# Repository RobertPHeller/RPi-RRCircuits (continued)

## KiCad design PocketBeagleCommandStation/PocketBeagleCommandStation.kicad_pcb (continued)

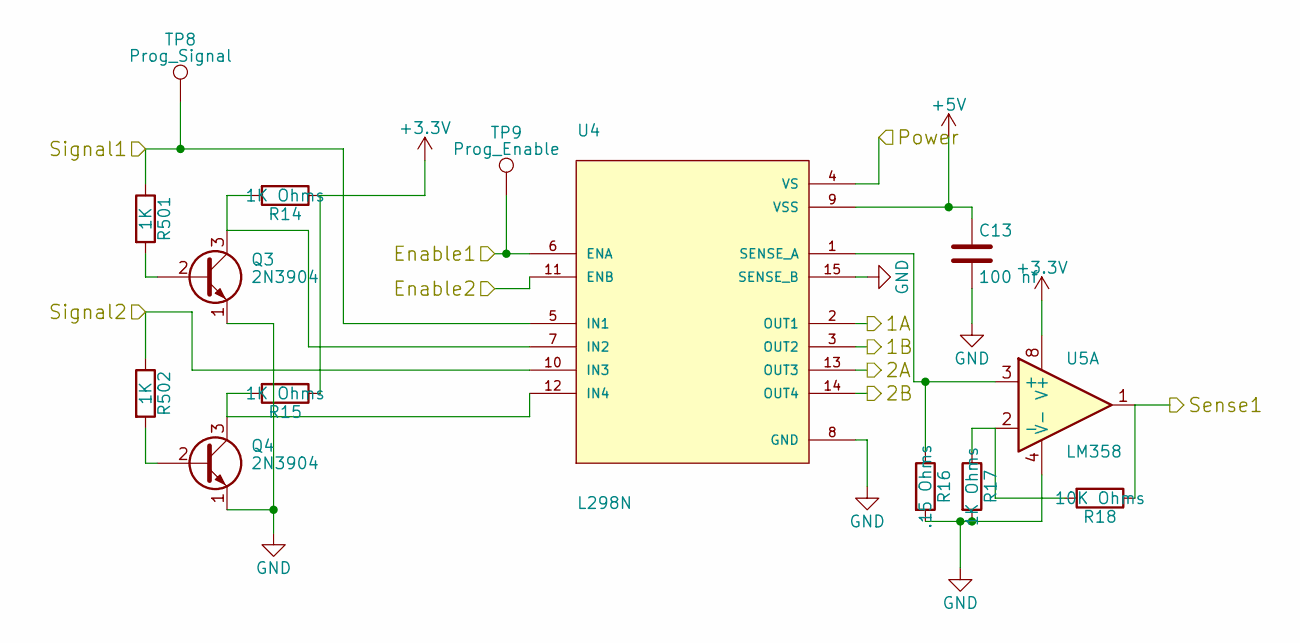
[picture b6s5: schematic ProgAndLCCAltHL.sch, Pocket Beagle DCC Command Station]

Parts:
C13: 100 nf; C_Rect_L4.0mm_W2.5mm_P2.50mm; Mouser Part Number 594-K104Z15Y5VF5TL2
Q3, Q4: 2N3904; TO-92_Molded_Narrow; Mouser Part Number 583-2N3904
R14, R15, R17: 1K Ohms; R_Axial_DIN0204_L3.6mm_D1.6mm_P2.54mm_Vertical; Mouser Part Number 603-MFR-12FTF52-1K
R16: .15 Ohms; R_Axial_DIN0204_L3.6mm_D1.6mm_P2.54mm_Vertical; Mouser Part Number MFR-25FTF52-0R15
R18: 10K Ohms; R_Axial_DIN0204_L3.6mm_D1.6mm_P2.54mm_Vertical; Mouser Part Number 603-MFR-12FTF52-10K
R501, R502: 1K; R_Axial_DIN0204_L3.6mm_D1.6mm_P2.54mm_Vertical; Mouser Part Number 603-MFR-12FTF52-1K
TP8: Prog_Signal; Measurement_Point_Round-TH_Small
TP9: Prog_Enable; Measurement_Point_Round-TH_Small
U4: L298N; TO127P2020X500X2100-15; Mouser Part Number 511-L298
U5: LM358; DIP-8_W7.62mm; Mouser Part Number 595-LM358AP

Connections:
+3V3: R14.1, R15.1, U5.8 (V+); also elsewhere on the board
+5V: C13.1, U4.9 (VSS); also elsewhere on the board
/OLBC_A: U4.13 (OUT3); also elsewhere on the board
/OLBC_B: U4.14 (OUT4); also elsewhere on the board
/OPS-ENABLE: U4.11 (ENB); also elsewhere on the board
/OPS-SIG: R502.1, U4.10 (IN3); also elsewhere on the board
/PROG-ENABLE: TP9.1, U4.6 (ENA); also elsewhere on the board
/PROG-SENSE: R18.1, U5.1; also elsewhere on the board
/PROG-SIG: R501.1, TP8.1, U4.5 (IN1); also elsewhere on the board
/PROG_DCC_VS: U4.4 (VS); also elsewhere on the board
/Prog and LCC Alt H/L Driver/1A: U4.2 (OUT1); also elsewhere on the board
/Prog and LCC Alt H/L Driver/1B: U4.3 (OUT2); also elsewhere on the board
GND: C13.2, Q3.1 (E), Q4.1 (E), R16.2, R17.2, U4.8 (GND), U4.15 (SENSE_B), U5.4 (V-); also elsewhere on the board
unnamed: Q3.2 (B), R501.2
unnamed: Q3.3 (C), R14.2, U4.7 (IN2)
unnamed: Q4.2 (B), R502.2
unnamed: Q4.3 (C), R15.2, U4.12 (IN4)
unnamed: R16.1, U4.1 (SENSE_A), U5.3 (+)
unnamed: R17.1, R18.2, U5.2 (-)

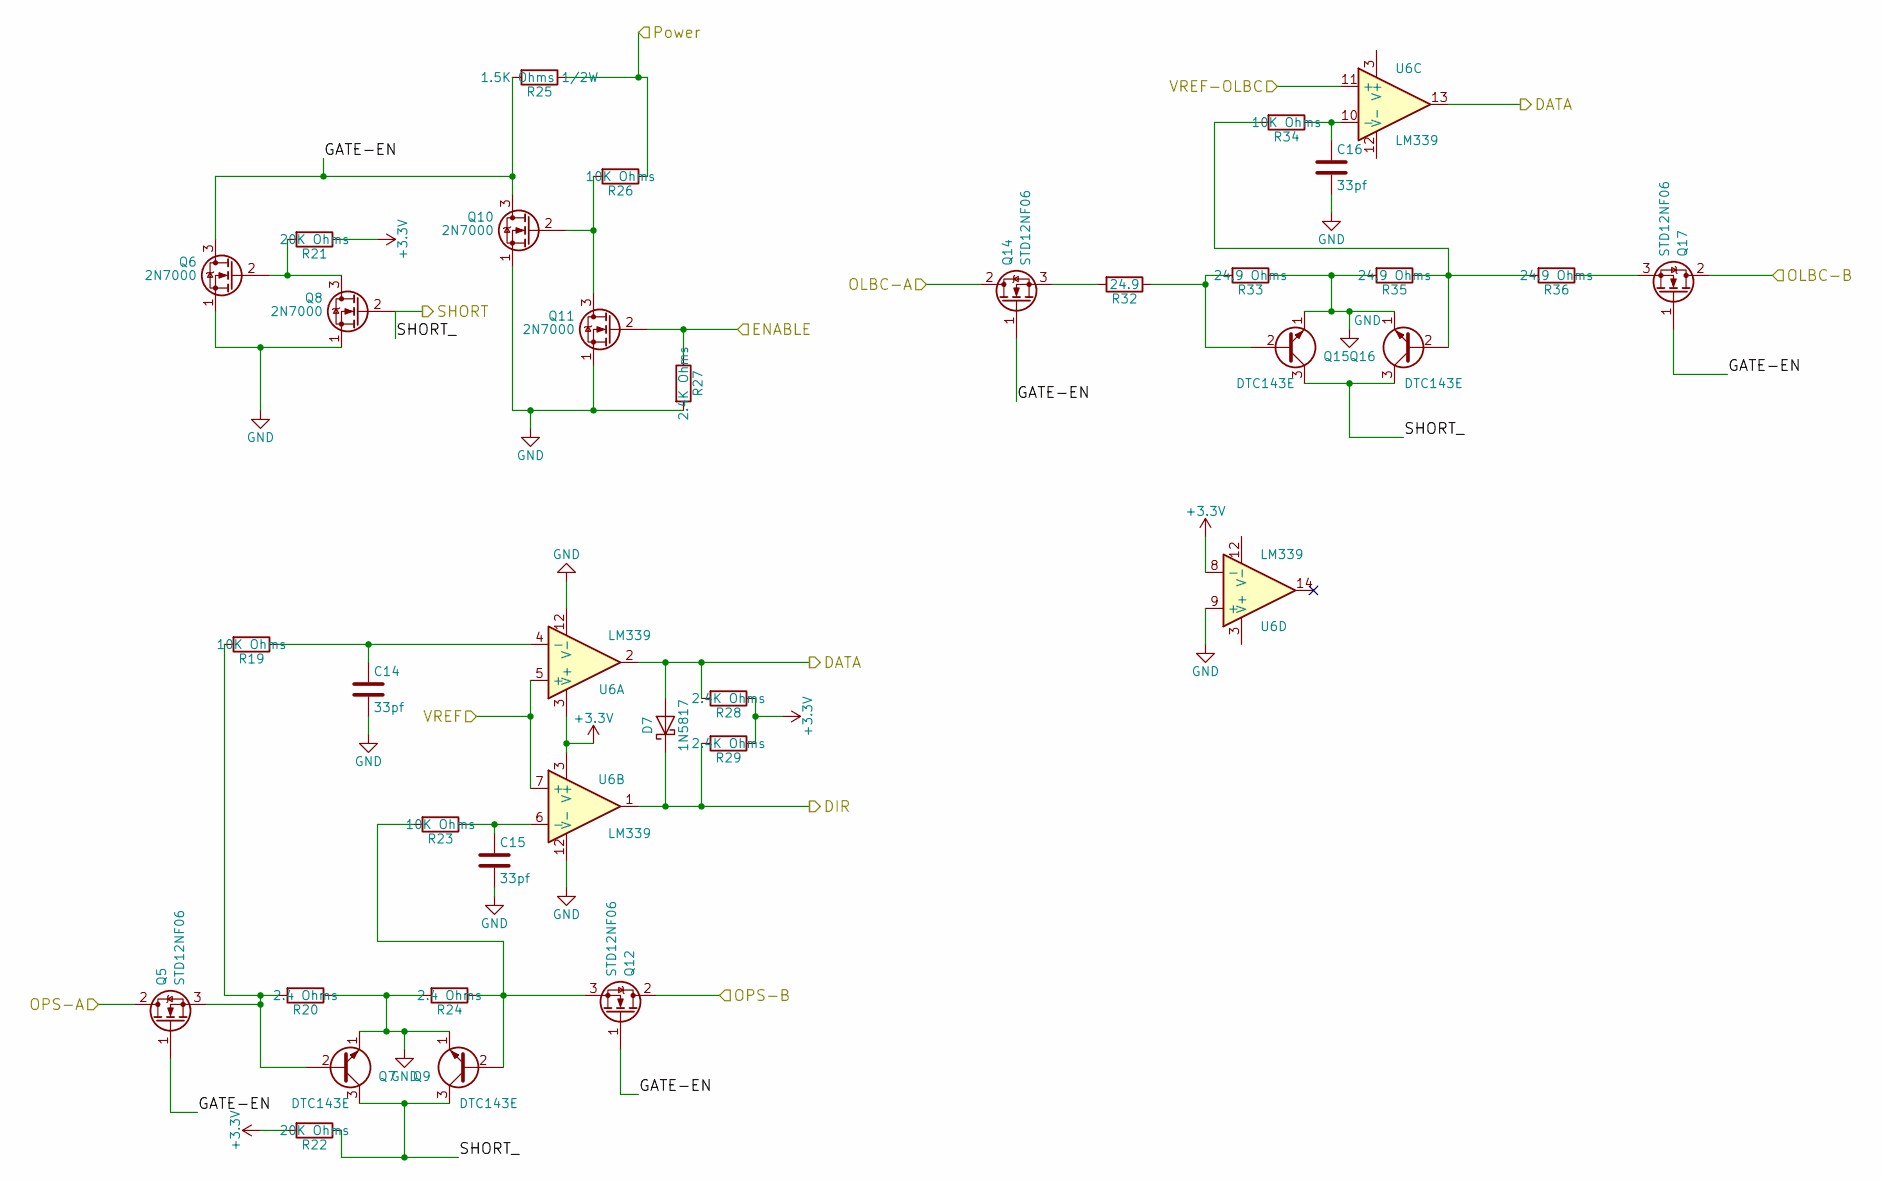
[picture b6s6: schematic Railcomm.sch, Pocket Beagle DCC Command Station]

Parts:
C14, C15, C16: 33pf; C_Rect_L4.0mm_W2.5mm_P2.50mm; Mouser Part Number 594-K330J10C0GH5TL2
D7: 1N5817; D_DO-41_SOD81_P7.62mm_Horizontal; Mouser Part Number 583-1N5817-T
Q5, Q12, Q14, Q17: STD12NF06; TO-251_IPAK_Vertical; Mouser Part Number 511-STD12NF06L-1
Q6, Q8, Q10, Q11: 2N7000; TO-92_Molded_Narrow; Mouser Part Number 512-2N7000BU
Q7, Q9, Q15, Q16: DTC143E; SOT-23_Handsoldering; Mouser Part Number 771-PDTC143ETT/R
R19, R23, R26: 10K Ohms; R_Axial_DIN0204_L3.6mm_D1.6mm_P2.54mm_Vertical; Mouser Part Number 603-MFR-12FTF52-10K
R20, R24: 2.4 Ohms; R_Axial_DIN0204_L3.6mm_D1.6mm_P2.54mm_Vertical; Mouser Part Number 603-CFR-25JB-52-2R4
R21, R22: 20K Ohms; R_Axial_DIN0204_L3.6mm_D1.6mm_P2.54mm_Vertical; Mouser Part Number 603-MFR-12FTF52-20K
R25: 1.5K Ohms 1/2W; R_Axial_DIN0204_L3.6mm_D1.6mm_P5.08mm_Vertical; Mouser Part Number 279-CFR25J1K5
R27, R28, R29: 2.4K Ohms; R_Axial_DIN0204_L3.6mm_D1.6mm_P2.54mm_Vertical; Mouser Part Number 660-CFS1/4CT52R242J
R32: 24.9; R_Axial_DIN0204_L3.6mm_D1.6mm_P1.90mm_Vertical; Mouser Part Number 71-CMF5524R900DHR6
R33, R35: 24.9 Ohms; R_Axial_DIN0204_L3.6mm_D1.6mm_P2.54mm_Vertical; Mouser Part Number 71-CMF5524R900DHR6
R34: 10K Ohms; R_Axial_DIN0204_L3.6mm_D1.6mm_P1.90mm_Vertical; Mouser Part Number 603-MFR-12FTF52-10K
R36: 24.9 Ohms; R_Axial_DIN0204_L3.6mm_D1.6mm_P1.90mm_Vertical; Mouser Part Number 71-CMF5524R900DHR6
U6: LM339; DIP-14_W7.62mm; Mouser Part Number 595-LM339N

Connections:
+3V3: R21.1, R22.2, R28.1, R29.1, U6.3 (V+), U6.8 (-); also elsewhere on the board
/DCC_VS: R25.1, R26.1; also elsewhere on the board
/OLBC_A: Q14.2 (D); also elsewhere on the board
/OLBC_B: Q17.2 (D); also elsewhere on the board
/OPS_A: Q5.2 (D); also elsewhere on the board
/OPS_B: Q12.2 (D); also elsewhere on the board
/RAILCOM-DATA: D7.2 (A), R28.2, U6.2, U6.13; also elsewhere on the board
/RAILCOM-DIR: D7.1 (K), R29.2, U6.1; also elsewhere on the board
/RAILCOM-ENABLE: Q11.2 (G), R27.1; also elsewhere on the board
/RAILCOM-SHORT: Q7.3 (C), Q8.2 (G), Q9.3 (C), Q15.3 (C), Q16.3 (C), R22.1; also elsewhere on the board
/RAILCOM_OLBC_VREF: U6.11 (+); also elsewhere on the board
/RAILCOM_VREF: U6.5 (+), U6.7 (+); also elsewhere on the board
/Railcomm Interface/GATE-EN: Q5.1 (G), Q6.3 (D), Q10.3 (D), Q12.1 (G), Q14.1 (G), Q17.1 (G), R25.2
GND: C14.2, C15.2, C16.2, Q6.1 (S), Q7.1 (E), Q8.1 (S), Q9.1 (E), Q10.1 (S), Q11.1 (S), Q15.1 (E), Q16.1 (E), R20.1, R24.2, R27.2, R33.1, R35.2, U6.9 (+), U6.12 (V-); also elsewhere on the board
unnamed: C14.1, R19.1, U6.4 (-)
unnamed: C15.1, R23.1, U6.6 (-)
unnamed: C16.1, R34.1, U6.10 (-)
unnamed: Q5.3 (S), Q7.2 (B), R19.2, R20.2
unnamed: Q6.2 (G), Q8.3 (D), R21.2
unnamed: Q10.2 (G), Q11.3 (D), R26.2
unnamed: Q9.2 (B), Q12.3 (S), R23.2, R24.1
unnamed: Q14.3 (S), R32.2
unnamed: Q15.2 (B), R32.1, R33.2
unnamed: Q16.2 (B), R34.2, R35.1, R36.2
unnamed: Q17.3 (S), R36.1

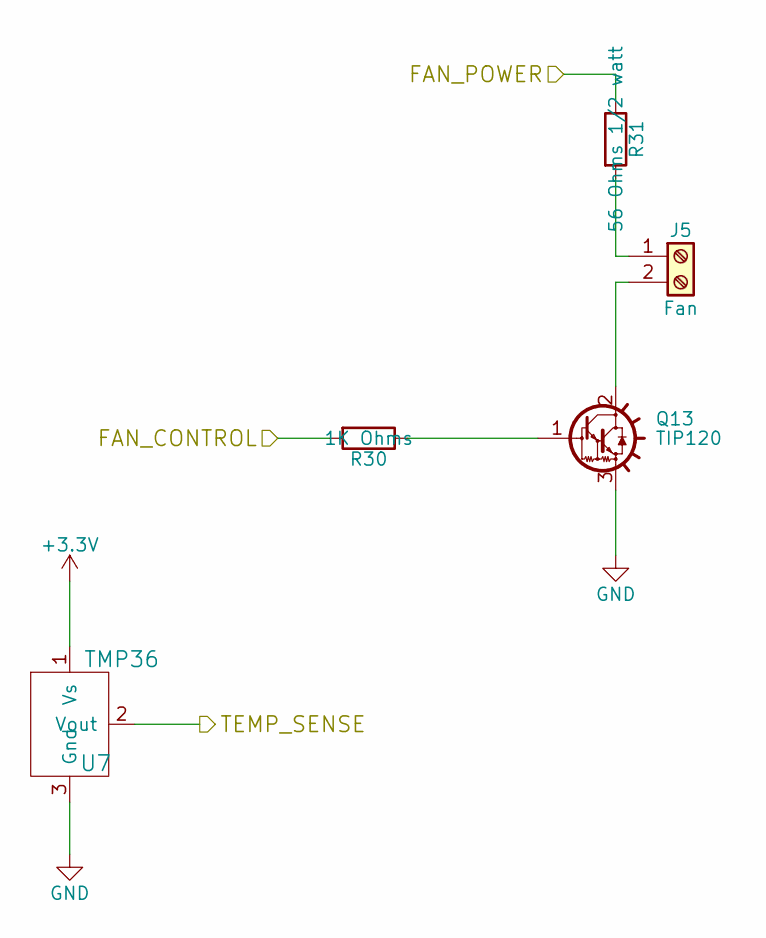
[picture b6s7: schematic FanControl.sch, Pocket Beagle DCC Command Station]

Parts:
J5: Fan; TerminalBlock_Pheonix_MPT-2.54mm_2pol; Mouser Part Number 651-1725656
Q13: TIP120; TO-220_Vertical; Mouser Part Number 583-TIP120
R30: 1K Ohms; R_Axial_DIN0204_L3.6mm_D1.6mm_P2.54mm_Vertical; Mouser Part Number 603-MFR-12FTF52-1K
R31: 56 Ohms 1/2 watt; R_Axial_DIN0204_L3.6mm_D1.6mm_P5.08mm_Vertical; Mouser Part Number 660-CF1/2CT52R560J
U7: TMP36; TO-92_Molded_Narrow; Mouser Part Number 485-165

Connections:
+3V3: U7.1 (Vs); also elsewhere on the board
/DCC_VS: R31.1; also elsewhere on the board
/FAN-CONTROL: R30.2; also elsewhere on the board
/TEMP-SENSE: U7.2 (Vout); also elsewhere on the board
GND: Q13.3 (E), U7.3 (Gnd); also elsewhere on the board
unnamed: J5.1, R31.2
unnamed: J5.2, Q13.2 (C)
unnamed: Q13.1 (B), R30.1

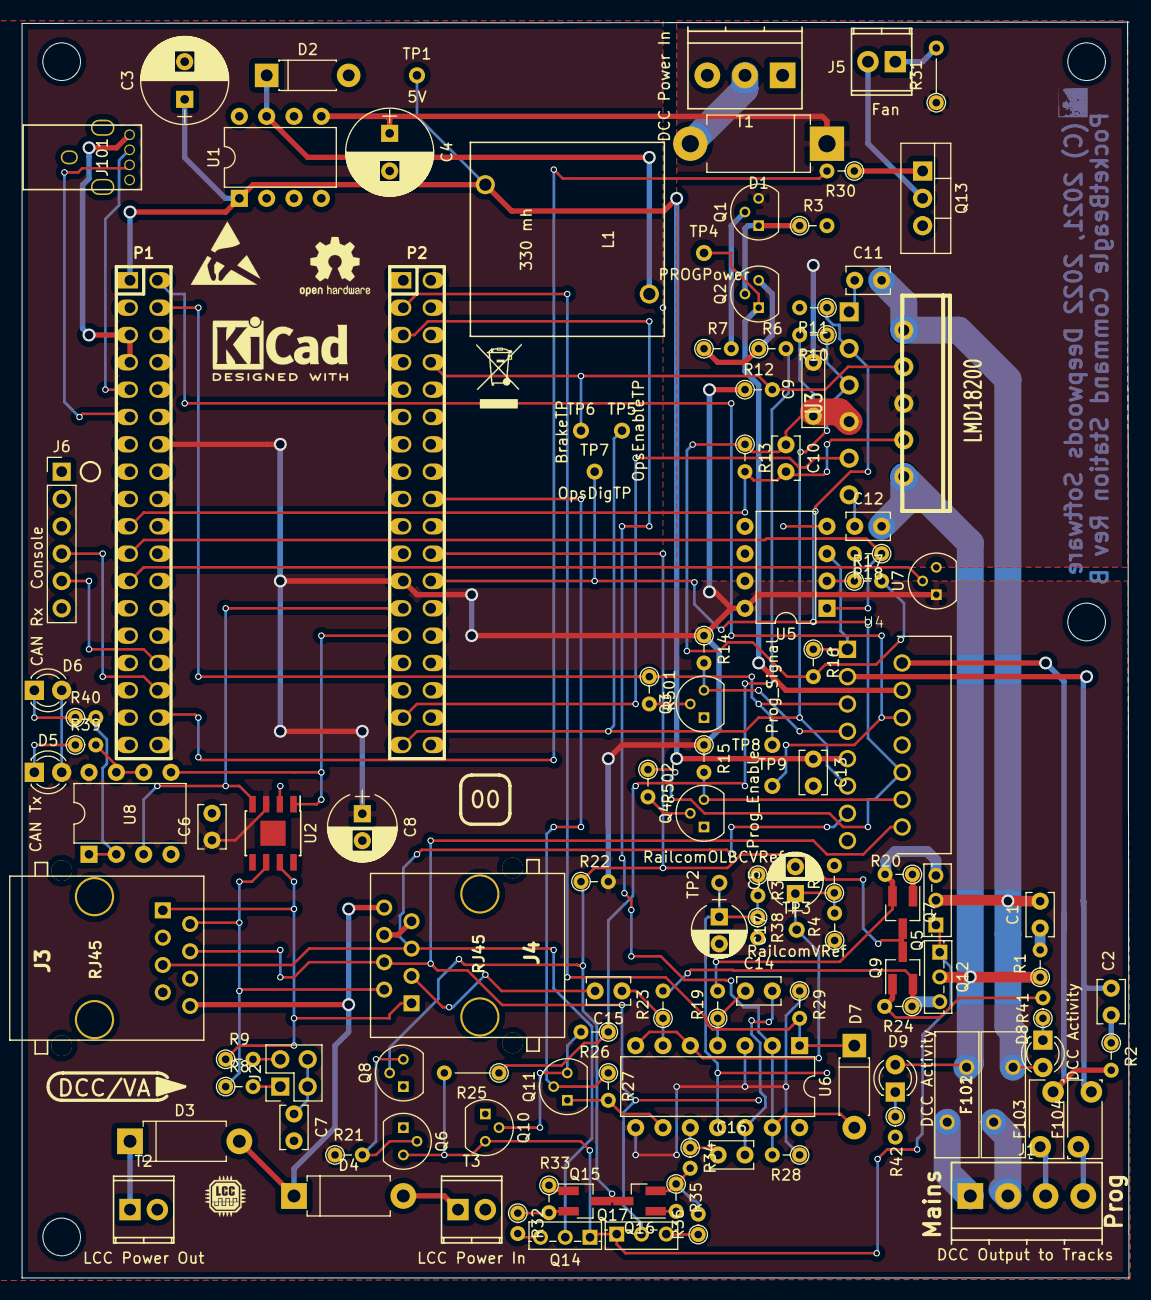
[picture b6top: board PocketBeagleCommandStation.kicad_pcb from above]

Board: 2 copper layers, 102.9 x 116.7 mm, 121 parts (0 on the bottom side), 82 nets.

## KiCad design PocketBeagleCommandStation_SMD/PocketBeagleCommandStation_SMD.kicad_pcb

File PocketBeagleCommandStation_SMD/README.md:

# PocketBeagleCommandStation_SMD

SMD version of the PocketBeagle LCC/DCC Command Station.  This is a
DCC command station that is a LCC node. It implements the OpenLCB train
protocol node over LCC and converts that to DCC commands. It includes a
booster and puts the DCC signal on the LCC bus (pins 4 and 5). It implements a
programming track and implements Railcom. The Command Station uses a
PocketBeagle as the processing element and uses the PRUs (Programmable
Realtime Units) to generate the DCC signal. (See
[PocketBeagleCommandStation](https://github.com/RobertPHeller/RPi-RRCircuits/tree/master/PocketBeagleCommandStation)
for a through hole version.)

* [Mouser Cart](https://www.mouser.com/ProjectManager/ProjectDetail.aspx?AccessID=b3caa67930)
* [Schematic PDF](https://github.com/RobertPHeller/RPi-RRCircuits/blob/master/PocketBeagleCommandStation_SMD/PocketBeagleCommandStation_SMD.pdf)
* [Board Rendering](https://github.com/RobertPHeller/RPi-RRCircuits/blob/master/PocketBeagleCommandStation_SMD/PocketBeagleCommandStation_SMD.png)
* [Node Software](https://github.com/RobertPHeller/RPi-RRCircuits/tree/master/BBBCommandStationOpenMRN)

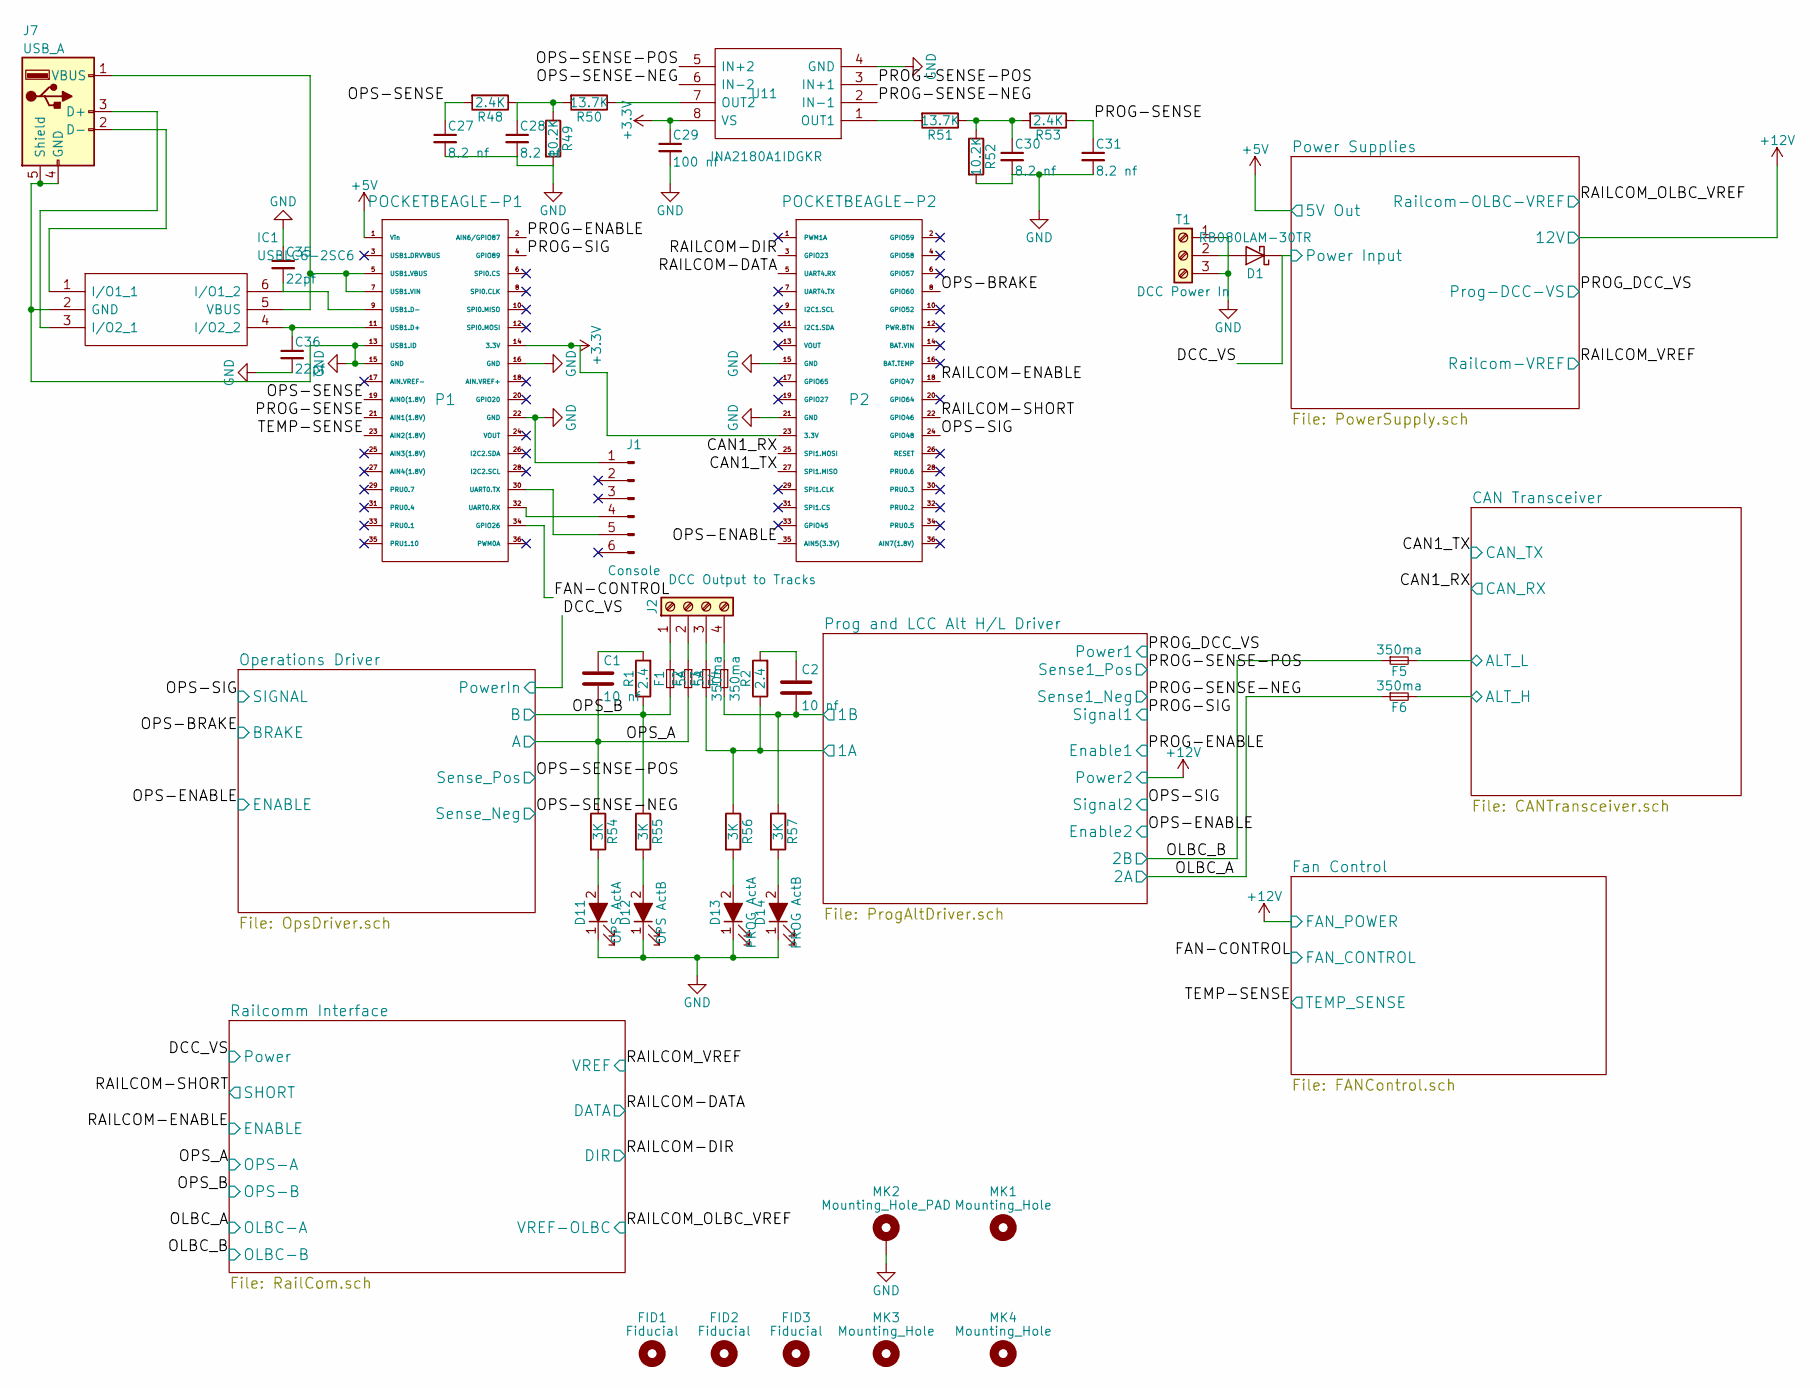
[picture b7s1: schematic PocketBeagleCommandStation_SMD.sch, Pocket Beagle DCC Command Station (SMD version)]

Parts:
C1, C2: 10 nf; C_1206; Mouser Part Number 791-1206B103K500CT
C27, C28, C30, C31: 8.2 nf; C_0603; Mouser Part Number 791-0603B822K250CT
C29: 100 nf; C_0603; Mouser Part Number 603-CC603KPX7R9BB104
C35, C36: 22pf; C_0402; Mouser Part Number 187-CL05C220JB5NNND
D1: RB080LAM-30TR; PMDTM; Mouser Part Number 755-RB080LAM-30TR
D11: OPS ActA; LED_0603; Mouser Part Number 710-150060GS75000
D12: OPS ActB; LED_0603; Mouser Part Number 710-150060RS75000
D13: PROG ActA; LED_0603; Mouser Part Number 710-150060GS75000
D14: PROG ActB; LED_0603; Mouser Part Number 710-150060RS75000
F1, F2: 5A; MFR500; Mouser Part Number 652-MFR500
F3, F4, F5, F6: 350ma; FUSC4632X70N; Mouser Part Number 530-0ZCG0035AF2C
FID1, FID2, FID3: Fiducial; Fiducial_Modern_CopperTop
IC1: USBLC6-2SC6; SOT-23-6; Mouser Part Number 511-USBLC6-2SC6
J1: Console; Pin_Header_Straight_1x06_Pitch2.54mm; Mouser Part Number 649-75160-156-06LF
J2: DCC Output to Tracks; TerminalBlock_Pheonix_PT-3.5mm_4pol; Mouser Part Number 651-5442264
J7: USB_A; 8964300490000000; Mouser Part Number 575-4300890
MK1, MK3, MK4: Mounting_Hole; MountingHole_3.2mm_M3
MK2: Mounting_Hole_PAD; MountingHole_3.2mm_M3_Pad_Via
P1: POCKETBEAGLE-P1; Socket_Strip_Straight_2x18_Pitch2.54mm; Mouser Part Number 517-929975-01-18-RK
P2: POCKETBEAGLE-P2; Socket_Strip_Straight_2x18_Pitch2.54mm; Mouser Part Number 517-929975-01-18-RK
R1, R2: 2.4; R_1206; Mouser Part Number 71-CRCW12062R40FKEA
R48, R53: 2.4K; R_0603; Mouser Part Number 667-ERJ-3EKF2401V
R49, R52: 10.2K; R_0603; Mouser Part Number 667-ERJ-3EKF1022V
R50, R51: 13.7K; R_0603; Mouser Part Number 652-CR0603FX-1372ELF
R54, R55, R56, R57: 3K; R_0603; Mouser Part Number 660-RN73H1JT3001F100
T1: DCC Power In; TerminalBlock_Pheonix_PT-3.5mm_3pol; Mouser Part Number 651-5442251
U11: INA2180A1IDGKR; SOP65P490X110-8N; Mouser Part Number 595-INA2180A1IDGKR

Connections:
+3V3: C29.1, P1.14 (3.3V), P2.23 (3.3V), U11.8 (VS); also elsewhere on the board
+5V: P1.1 (Vin); also elsewhere on the board
/CAN1_RX: P2.25 (SPI1.MOSI); also elsewhere on the board
/CAN1_TX: P2.27 (SPI1.MISO); also elsewhere on the board
/CAN Transceiver/ALT_H: F6.2; also elsewhere on the board
/CAN Transceiver/ALT_L: F5.2; also elsewhere on the board
/DCC_VS: D1.1 (K), U11.5 (IN+2); also elsewhere on the board
/FAN-CONTROL: P1.34 (GPIO26); also elsewhere on the board
/OLBC_A: F6.1; also elsewhere on the board
/OLBC_B: F5.1; also elsewhere on the board
/OPS-BRAKE: P2.8 (GPIO60); also elsewhere on the board
/OPS-ENABLE: P2.35 (AIN5(3.3V)); also elsewhere on the board
/OPS-SENSE: C27.1, P1.19 (AIN0(1.8V)), R48.2
/OPS-SENSE-NEG: U11.6 (IN-2); also elsewhere on the board
/OPS-SIG: P2.24 (GPIO48); also elsewhere on the board
/OPS_A: C1.2, F2.2, R54.1; also elsewhere on the board
/OPS_B: F1.2, R1.1, R55.1; also elsewhere on the board
/PROG-ENABLE: P1.2 (AIN6/GPIO87); also elsewhere on the board
/PROG-SENSE: C31.1, P1.21 (AIN1(1.8V)), R53.1
/PROG-SENSE-NEG: U11.2 (IN-1); also elsewhere on the board
/PROG-SENSE-POS: U11.3 (IN+1); also elsewhere on the board
/PROG-SIG: P1.4 (GPIO89); also elsewhere on the board
/Prog and LCC Alt H/L Driver/1A: F3.2, R2.1, R56.1; also elsewhere on the board
/Prog and LCC Alt H/L Driver/1B: C2.2, F4.2, R57.1; also elsewhere on the board
/RAILCOM-DATA: P2.5 (UART4.RX); also elsewhere on the board
/RAILCOM-DIR: P2.3 (GPIO23); also elsewhere on the board
/RAILCOM-ENABLE: P2.18 (GPIO47); also elsewhere on the board
/RAILCOM-SHORT: P2.22 (GPIO46); also elsewhere on the board
/TEMP-SENSE: P1.23 (AIN2(1.8V)); also elsewhere on the board
GND: C27.2, C28.2, C29.2, C30.2, C31.2, C35.1, C36.2, D11.1 (K), D12.1 (K), D13.1 (K), D14.1 (K), IC1.2 (GND), J1.1, J7.4 (GND), J7.5 (Shield), MK2.1, P1.13 (USB1.ID), P1.15 (GND), P1.16 (GND), P1.22 (GND), P2.15 (GND), P2.21 (GND), R49.2, R52.2, T1.1, T1.3, U11.4 (GND); also elsewhere on the board
unnamed: C1.1, R1.2
unnamed: C2.1, R2.2
unnamed: C28.1, R48.1, R49.1, R50.2
unnamed: C30.1, R51.1, R52.1, R53.2
unnamed: C35.2, IC1.6 (I/O1_2), P1.9 (USB1.D-)
unnamed: C36.1, IC1.4 (I/O2_2), P1.11 (USB1.D+)
unnamed: D1.2 (A), T1.2
unnamed: D11.2 (A), R54.2
unnamed: D12.2 (A), R55.2
unnamed: D13.2 (A), R56.2
unnamed: D14.2 (A), R57.2
unnamed: F1.1, J2.1
unnamed: F2.1, J2.2
unnamed: F3.1, J2.3
unnamed: F4.1, J2.4
unnamed: IC1.1 (I/O1_1), J7.2 (D-)
unnamed: IC1.3 (I/O2_1), J7.3 (D+)
unnamed: IC1.5 (VBUS), J7.1 (VBUS), P1.5 (USB1.VBUS), P1.7 (USB1.VIN)
unnamed: J1.4, P1.32 (UART0.RX)
unnamed: J1.5, P1.30 (UART0.TX)
unnamed: R50.1, U11.7 (OUT2)
unnamed: R51.2, U11.1 (OUT1)

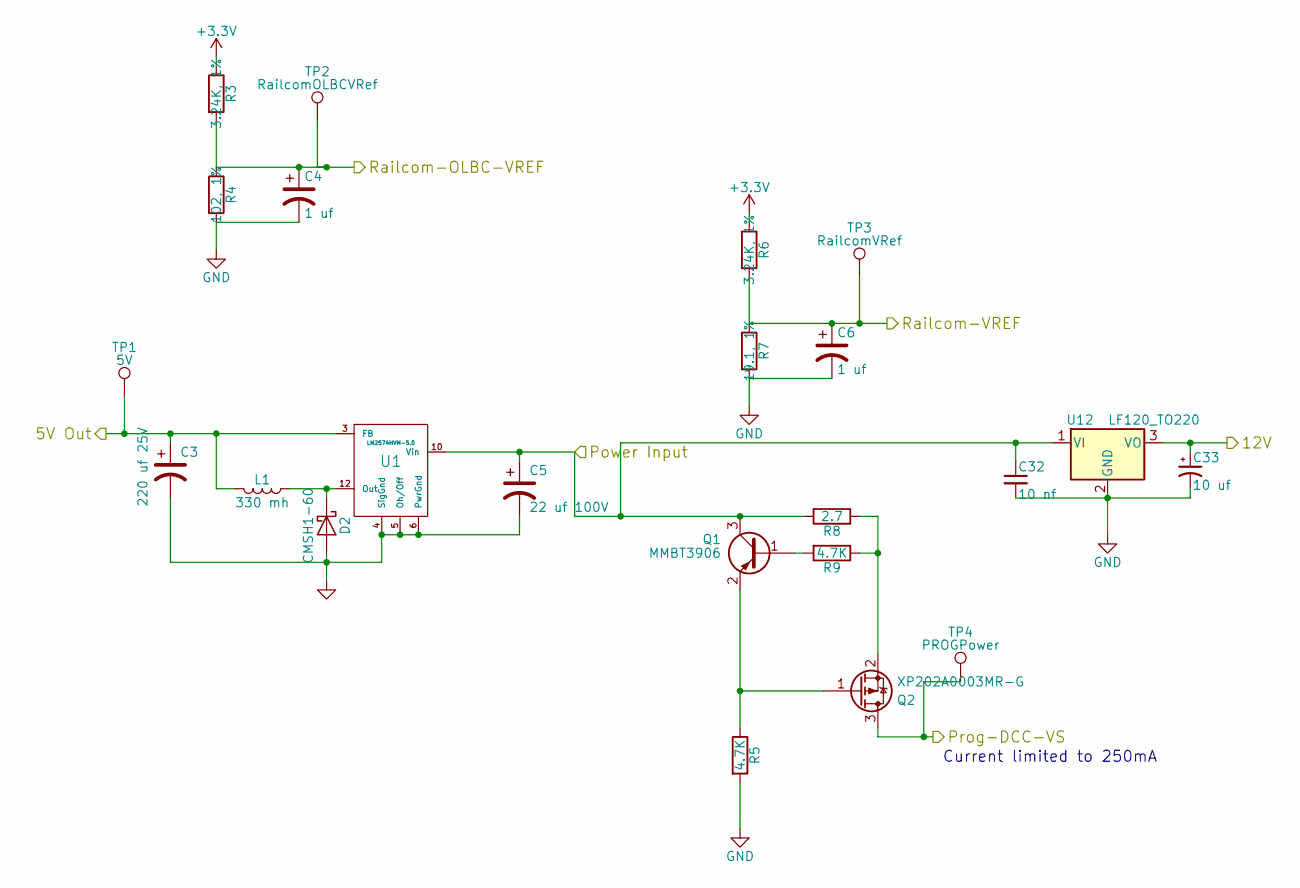
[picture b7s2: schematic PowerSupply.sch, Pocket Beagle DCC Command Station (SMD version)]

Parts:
C3: 220 uf 25V; CP_Elec_8x10; Mouser Part Number 647-UUX2A220MNL6GS
C4, C6: 1 uf; C_0603; Mouser Part Number 963-GMK107AB7105KAHT
C5: 22 uf 100V; CP_Elec_8x10; Mouser Part Number 647-UWT1E221MNL1GS
C32: 10 nf; C_1206; Mouser Part Number 791-1206B103K500CT
C33: 10 uf; CP_Elec_5x5.3; Mouser Part Number 710-865230542002
D2: CMSH1-60; D_SMA; Mouser Part Number 610-CMSH1-60TR13
L1: 330 mh; SRN1060; Mouser Part Number 652-SRN1060-331M
Q1: MMBT3906; SOT-23; Mouser Part Number 583-MMBT3906
Q2: XP202A0003MR-G; SOT-23; Mouser Part Number 865-XP202A0003MR-G
R3, R6: 3.24K, 1%; R_0603; Mouser Part Number 652-CR0603FX-1803ELF
R4: 102, 1%; R_0805; Mouser Part Number 71-CRCW0805102RFKEA
R5, R9: 4.7K; R_0805; Mouser Part Number 71-CRCW0805-4.7K-E3
R7: 19.1, 1%; R_0805; Mouser Part Number 71-CRCW080519R1FKEA
R8: 2.7; R_1206; Mouser Part Number 660-RK73H2BTTD2R70F
TP1: 5V; Measurement_Point_Round-SMD-Pad_Big
TP2: RailcomOLBCVRef; Measurement_Point_Round-SMD-Pad_Big
TP3: RailcomVRef; Measurement_Point_Round-SMD-Pad_Big
TP4: PROGPower; Measurement_Point_Round-SMD-Pad_Big
U1: LM2574HVM-5.0; SOIC-14_7.4x8.7mm_Pitch1.27mm; Mouser Part Number 926-LM2574N-5.0/NOPB
U12: LF120_TO220; TO-252-2; Mouser Part Number 511-LF120ABDT-TR

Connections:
+3V3: R3.1, R6.1; also elsewhere on the board
+5V: C3.1, L1.2, TP1.1, U1.3 (FB); also elsewhere on the board
+12V: C33.1, U12.3 (VO); also elsewhere on the board
/DCC_VS: C5.1, C32.1, Q1.3 (C), R8.2, U1.10 (Vin), U12.1 (VI); also elsewhere on the board
/PROG-SENSE-POS: Q2.3 (D), TP4.1; also elsewhere on the board
/RAILCOM_OLBC_VREF: C4.1, R3.2, R4.1, TP2.1; also elsewhere on the board
/RAILCOM_VREF: C6.1, R6.2, R7.1, TP3.1; also elsewhere on the board
GND: C3.2, C4.2, C5.2, C6.2, C32.2, C33.2, D2.2 (A), R4.2, R5.2, R7.2, U1.4 (SigGnd), U1.5 (Oh/Off), U1.6 (PwrGnd), U12.2 (GND); also elsewhere on the board
unnamed: D2.1 (K), L1.1, U1.12 (Out)
unnamed: Q1.1 (B), R9.2
unnamed: Q1.2 (E), Q2.1 (G), R5.1
unnamed: Q2.2 (S), R8.1, R9.1

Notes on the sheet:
Current limited to 250mA

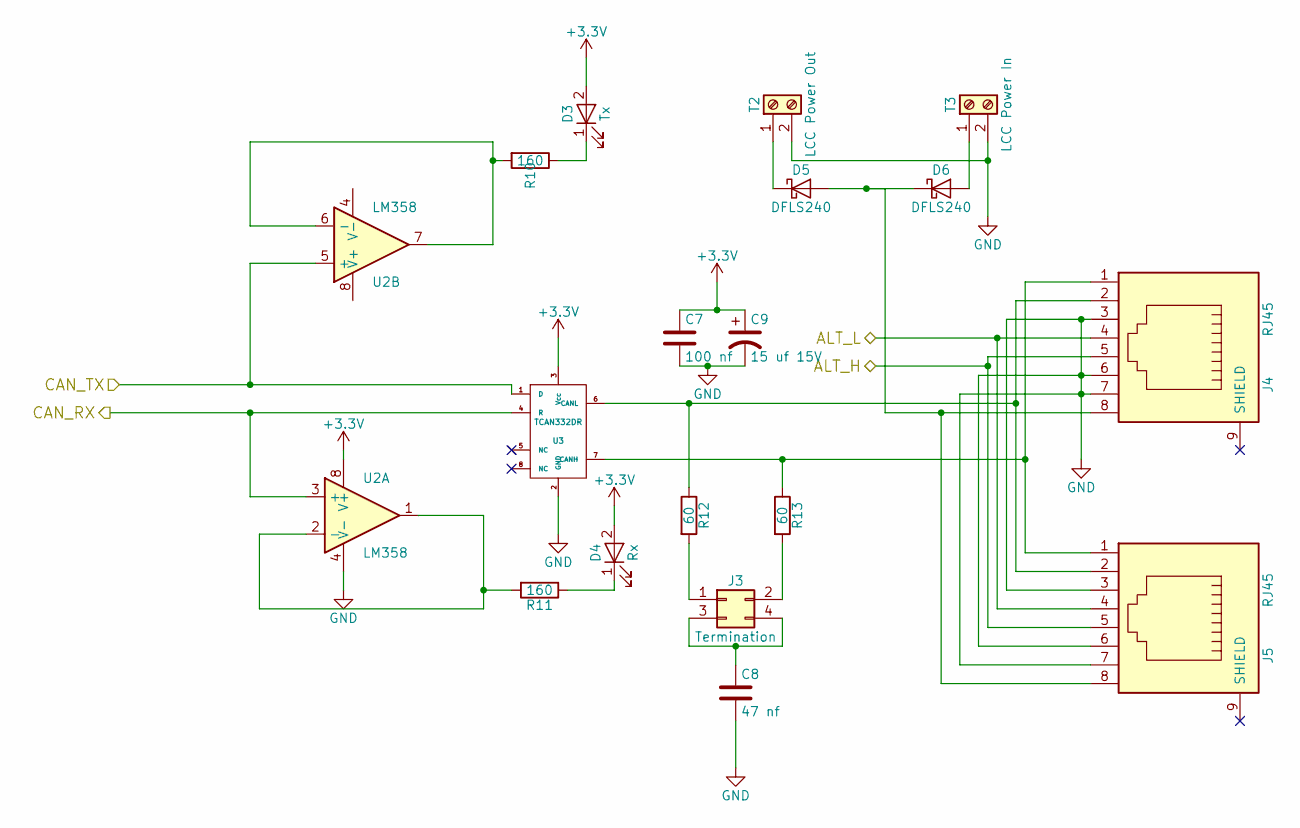
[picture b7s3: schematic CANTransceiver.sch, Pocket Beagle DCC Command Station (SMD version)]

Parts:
C7: 100 nf; C_0603; Mouser Part Number 603-CC603KPX7R9BB104
C8: 47 nf; C_0603; Mouser Part Number 963-GMK107BJ473KAHT
C9: 15 uf 15V; CP_Elec_4x5.8; Mouser Part Number 647-UUD1C150MCL
D3: Tx; LED_0603; Mouser Part Number 710-150060SS75000
D4: Rx; LED_0603; Mouser Part Number 710-150060YS75000
D5, D6: DFLS240; D_SMB; Mouser Part Number 621-DFLS240-7
J3: Termination; Pin_Header_Straight_2x02_Pitch2.54mm; Mouser Part Number 538-90131-0122
J4, J5: RJ45; RJ45_8N-S; Mouser Part Number 710-615008144221
R10, R11: 160; R_0603; Mouser Part Number 603-AC0603JR-07160RL
R12, R13: 60; R_1206; Mouser Part Number 71-CRCW120660R0KNAIF
T2: LCC Power Out; TerminalBlock_Pheonix_MPT-2.54mm_2pol; Mouser Part Number 651-1725656
T3: LCC Power In; TerminalBlock_Pheonix_MPT-2.54mm_2pol; Mouser Part Number 651-1725656
U2: LM358; SOIC-8_3.9x4.9mm_Pitch1.27mm; Mouser Part Number 595-LM358BIDR
U3: TCAN332DR; SOIC-8-1EP_3.9x4.9mm_Pitch1.27mm; Mouser Part Number 595-TCAN332DR

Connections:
+3V3: C7.1, C9.1, D3.2 (A), D4.2 (A), U2.8 (V+), U3.3 (Vcc); also elsewhere on the board
/CAN1_RX: U2.3 (+), U3.4 (R); also elsewhere on the board
/CAN1_TX: U2.5 (+), U3.1 (D); also elsewhere on the board
/CAN Transceiver/ALT_H: J4.5, J5.5; also elsewhere on the board
/CAN Transceiver/ALT_L: J4.4, J5.4; also elsewhere on the board
GND: C7.2, C8.2, C9.2, J4.3, J4.6, J4.7, J5.3, J5.6, J5.7, T2.2, T3.2, U2.4 (V-), U3.2 (GND); also elsewhere on the board
unnamed: C8.1, J3.3, J3.4
unnamed: D3.1 (K), R10.1
unnamed: D4.1 (K), R11.1
unnamed: D5.1 (K), T2.1
unnamed: D5.2 (A), D6.1 (K), J4.8, J5.8
unnamed: D6.2 (A), T3.1
unnamed: J3.1, R12.2
unnamed: J3.2, R13.2
unnamed: J4.1, J5.1, R13.1, U3.7 (CANH)
unnamed: J4.2, J5.2, R12.1, U3.6 (CANL)
unnamed: R10.2, U2.6 (-), U2.7
unnamed: R11.2, U2.1, U2.2 (-)

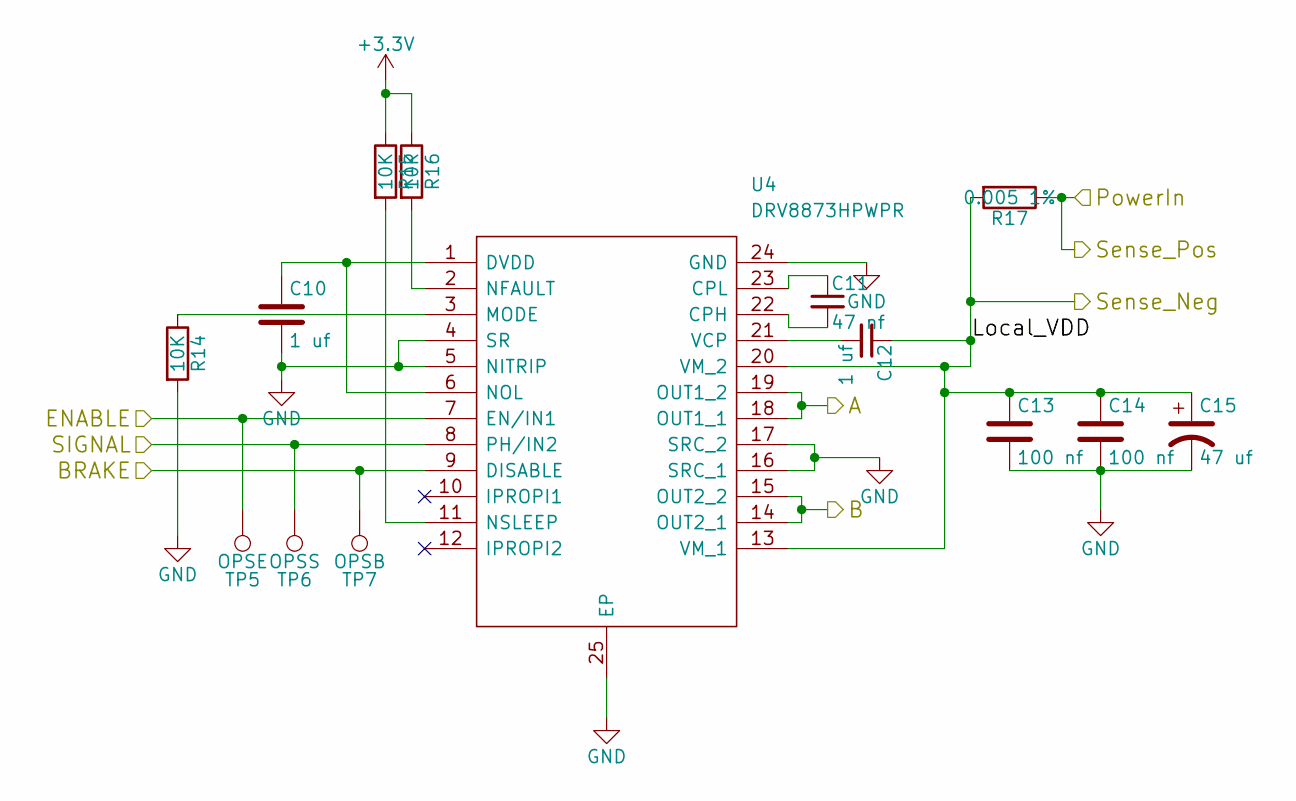
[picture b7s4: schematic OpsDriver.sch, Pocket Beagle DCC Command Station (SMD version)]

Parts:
C10, C12: 1 uf; C_0603; Mouser Part Number 963-GMK107AB7105KAHT
C11: 47 nf; C_0603; Mouser Part Number 963-GMK107BJ473KAHT
C13, C14: 100 nf; C_0603; Mouser Part Number 603-CC603KPX7R9BB104
C15: 47 uf; CP_Elec_6.3x5.3; Mouser Part Number 710-865080543009
R14, R15, R16: 10K; R_0603; Mouser Part Number 279-CRGCQ0603F10K
R17: 0.005 1%; R_0612; Mouser Part Number 71-WSKW0612L5000FEA
TP5: OPSE; Measurement_Point_Round-SMD-Pad_Big
TP6: OPSS; Measurement_Point_Round-SMD-Pad_Big
TP7: OPSB; Measurement_Point_Round-SMD-Pad_Big
U4: DRV8873HPWPR; SOP65P640X120-25N; Mouser Part Number 595-DRV8873HPWPR

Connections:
+3V3: R15.1, R16.1; also elsewhere on the board
/DCC_VS: R17.1; also elsewhere on the board
/OPS-BRAKE: TP7.1, U4.9 (DISABLE); also elsewhere on the board
/OPS-ENABLE: TP5.1, U4.7 (EN/IN1); also elsewhere on the board
/OPS-SENSE-NEG: C12.1, C13.1, C14.1, C15.1, R17.2, U4.13 (VM_1), U4.20 (VM_2); also elsewhere on the board
/OPS-SIG: TP6.1, U4.8 (PH/IN2); also elsewhere on the board
/OPS_A: U4.18 (OUT1_1), U4.19 (OUT1_2); also elsewhere on the board
/OPS_B: U4.14 (OUT2_1), U4.15 (OUT2_2); also elsewhere on the board
GND: C10.2, C13.2, C14.2, C15.2, R14.2, U4.4 (SR), U4.5 (NITRIP), U4.16 (SRC_1), U4.17 (SRC_2), U4.24 (GND), U4.25 (EP); also elsewhere on the board
unnamed: C10.1, U4.1 (DVDD), U4.6 (NOL)
unnamed: C11.1, U4.23 (CPL)
unnamed: C11.2, U4.22 (CPH)
unnamed: C12.2, U4.21 (VCP)
unnamed: R14.1, U4.3 (MODE)
unnamed: R15.2, U4.11 (NSLEEP)
unnamed: R16.2, U4.2 (NFAULT)
